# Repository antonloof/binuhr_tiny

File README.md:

# binuhr_tiny
a small binary clock, so cute &lt;3

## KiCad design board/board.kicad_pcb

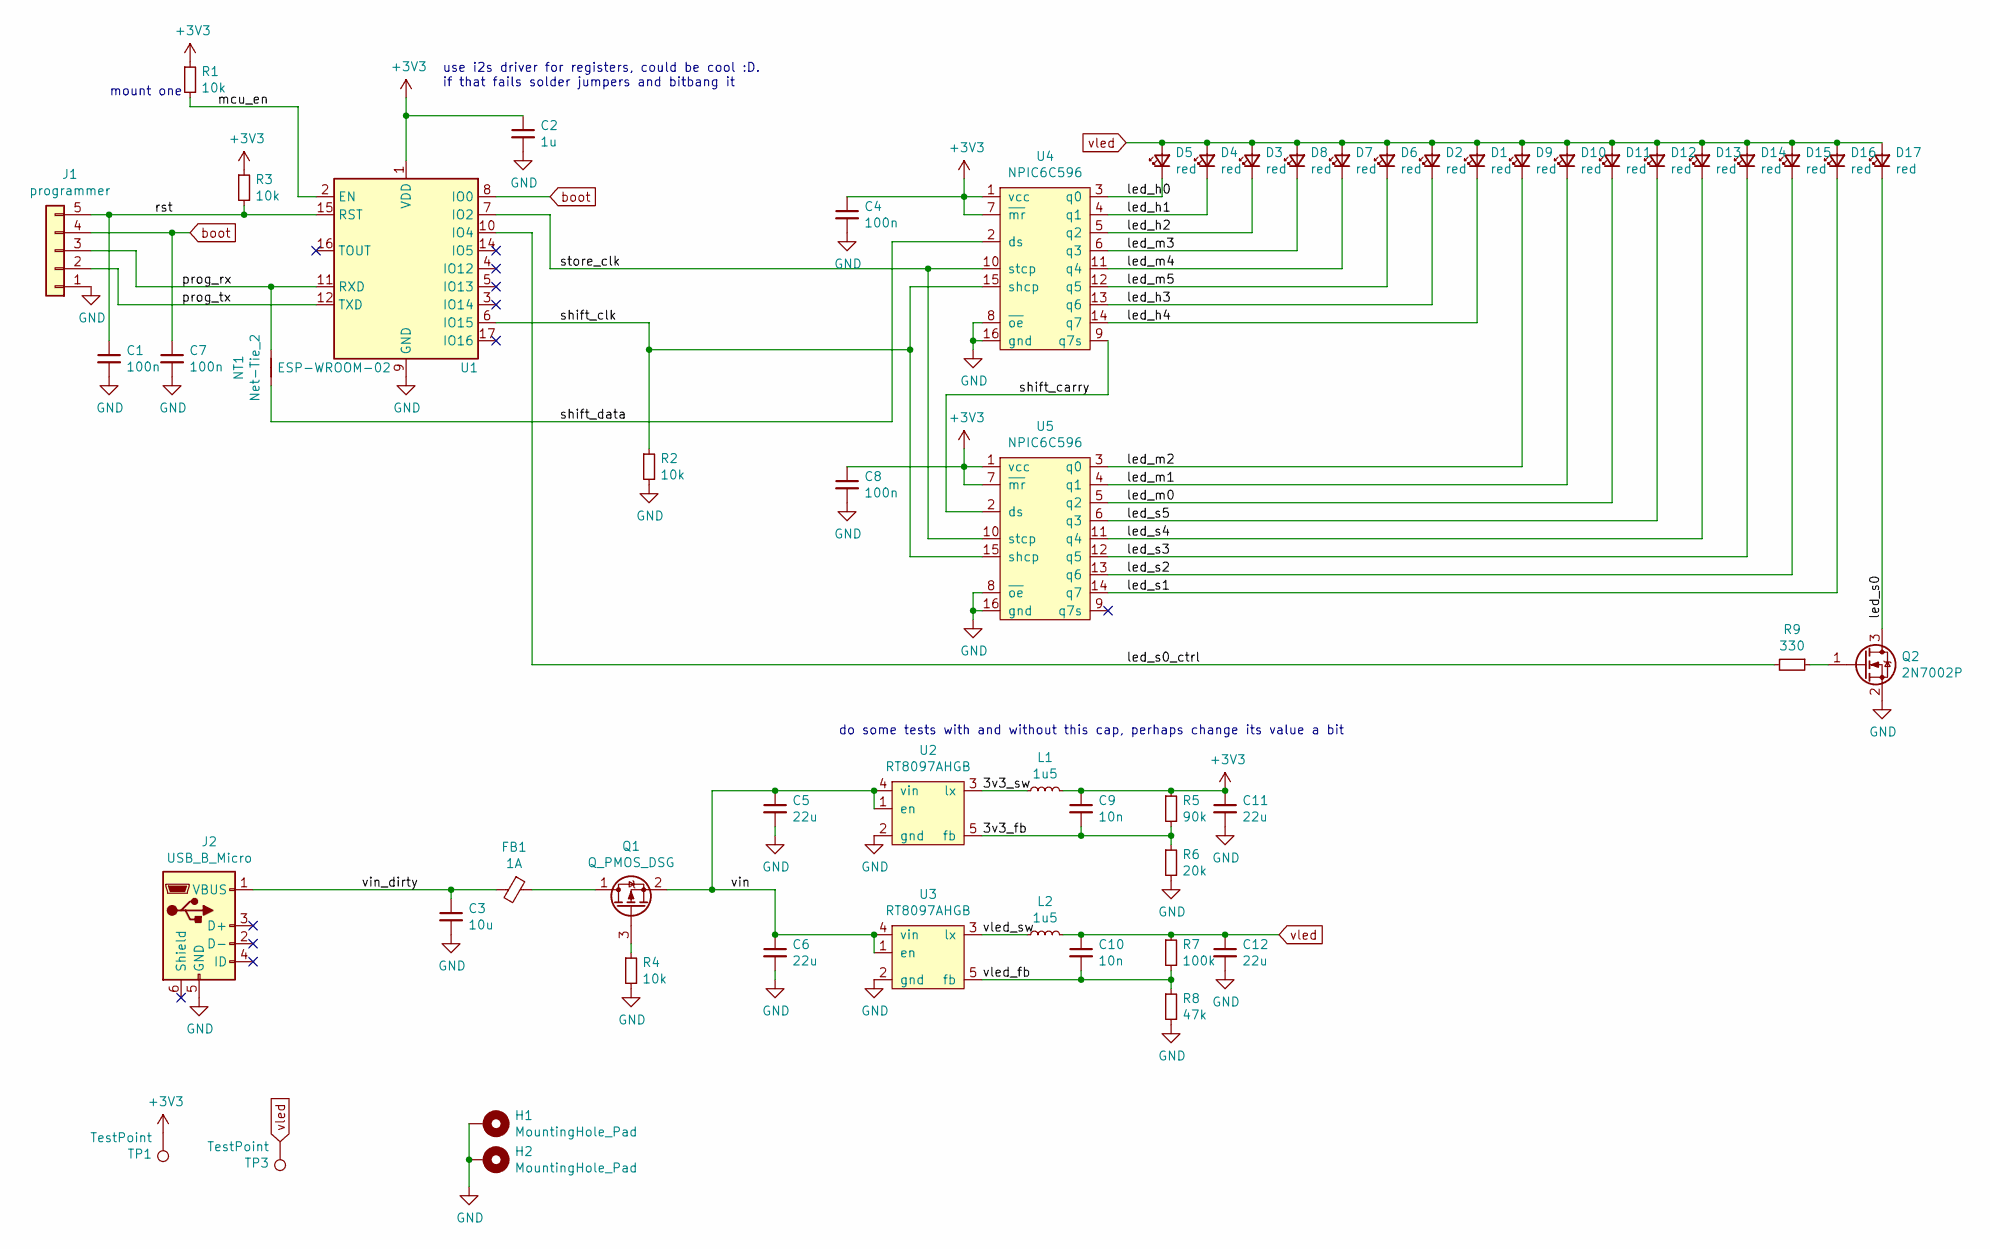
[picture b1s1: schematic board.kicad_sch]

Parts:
C1, C4, C7, C8: 100n; C_0603_1608Metric
C2: 1u; C_0603_1608Metric
C3: 10u; C_0603_1608Metric
C5, C6, C11, C12: 22u; C_0603_1608Metric
C9, C10: 10n; C_0603_1608Metric
D1, D2, D3, D4, D5, D6, D7, D8, D9, D10, D11, D12, D13, D14, D15, D16, D17: red; LED_1210_3225Metric
FB1: 1A; L_0603_1608Metric_Pad1.05x0.95mm_HandSolder
H1, H2: MountingHole_Pad; MountingHole_2.2mm_M2_ISO7380_Pad
J1: programmer; TSM-105-01-L_SH
J2: USB_B_Micro; USB_MICRO_10118193-0001LF
L1, L2: 1u5; L_Sunlord_MWSA0518_5.4x5.2mm
NT1: Net-Tie_2; NetTie-2_SMD_Pad0.5mm
Q1: Q_PMOS_DSG; SOT-23
Q2: 2N7002P; SOT-23
R1, R2, R3, R4: 10k; R_0603_1608Metric
R5: 90k; R_0603_1608Metric
R6: 20k; R_0603_1608Metric
R7: 100k; R_0603_1608Metric
R8: 47k; R_0603_1608Metric
R9: 330; R_0603_1608Metric
TP1, TP3: TestPoint; TestPoint_Pad_D1.5mm
U1: ESP-WROOM-02
U2, U3: RT8097AHGB; SOT-23-5_HandSoldering
U4, U5: NPIC6C596; STC_SOP-16_3.9x9.9mm_P1.27mm

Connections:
+3V3: C2.1, C4.1, C8.1, C9.1, C11.1, L1.2, R1.1, R3.1, R5.1, TP1.1, U1.1 (VDD), U4.1 (vcc), U4.7 (~mr), U5.1 (vcc), U5.7 (~mr)
/3v3_fb: C9.2, R5.2, R6.1, U2.5 (fb)
/3v3_sw: L1.1, U2.3 (lx)
/led_h0: D5.1 (K), U4.3 (q0)
/led_h1: D4.1 (K), U4.4 (q1)
/led_h2: D3.1 (K), U4.5 (q2)
/led_h3: D2.1 (K), U4.13 (q6)
/led_h4: D1.1 (K), U4.14 (q7)
/led_m0: D11.1 (K), U5.5 (q2)
/led_m1: D10.1 (K), U5.4 (q1)
/led_m2: D9.1 (K), U5.3 (q0)
/led_m3: D8.1 (K), U4.6 (q3)
/led_m4: D7.1 (K), U4.11 (q4)
/led_m5: D6.1 (K), U4.12 (q5)
/led_s0: D17.1 (K), Q2.3 (D)
/led_s0_ctrl: R9.2, U1.10 (IO4)
/led_s1: D16.1 (K), U5.14 (q7)
/led_s2: D15.1 (K), U5.13 (q6)
/led_s3: D14.1 (K), U5.12 (q5)
/led_s4: D13.1 (K), U5.11 (q4)
/led_s5: D12.1 (K), U5.6 (q3)
/mcu_en: R1.2, U1.2 (EN)
/prog_rx: J1.3, NT1.2, U1.11 (RXD)
/prog_tx: J1.2, U1.12 (TXD)
/rst: C1.1, J1.5, R3.2, U1.15 (RST)
/shift_carry: U4.9 (q7s), U5.2 (ds)
/shift_clk: R2.1, U1.6 (IO15), U4.15 (shcp), U5.15 (shcp)
/shift_data: NT1.1, U4.2 (ds)
/store_clk: U1.7 (IO2), U4.10 (stcp), U5.10 (stcp)
/vin: C5.1, C6.1, Q1.2 (S), U2.1 (en), U2.4 (vin), U3.1 (en), U3.4 (vin)
/vin_dirty: C3.1, FB1.2, J2.1 (VBUS)
/vled_fb: C10.2, R7.2, R8.1, U3.5 (fb)
/vled_sw: L2.1, U3.3 (lx)
GND: C1.2, C2.2, C3.2, C4.2, C5.2, C6.2, C7.2, C8.2, C11.2, C12.2, H1.1, H2.1, J1.1, J2.5 (GND), Q2.2 (S), R2.2, R4.2, R6.2, R8.2, U1.9 (GND), U1.13 (GND), U1.18 (GND), U1.19 (GND), U2.2 (gnd), U3.2 (gnd), U4.8 (~oe), U4.16 (gnd), U5.8 (~oe), U5.16 (gnd)
unnamed: FB1.1, Q1.1 (D)
unnamed: Q1.3 (G), R4.1
unnamed: Q2.1 (G), R9.1
boot: C7.1, J1.4, U1.8 (IO0)
vled: C10.1, C12.1, D1.2 (A), D2.2 (A), D3.2 (A), D4.2 (A), D5.2 (A), D6.2 (A), D7.2 (A), D8.2 (A), D9.2 (A), D10.2 (A), D11.2 (A), D12.2 (A), D13.2 (A), D14.2 (A), D15.2 (A), D16.2 (A), D17.2 (A), L2.2, R7.1, TP3.1

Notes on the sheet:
mount one
use i2s driver for registers, could be cool :D. if that fails solder jumpers and bitbang it
do some tests with and without this cap, perhaps change its value a bit

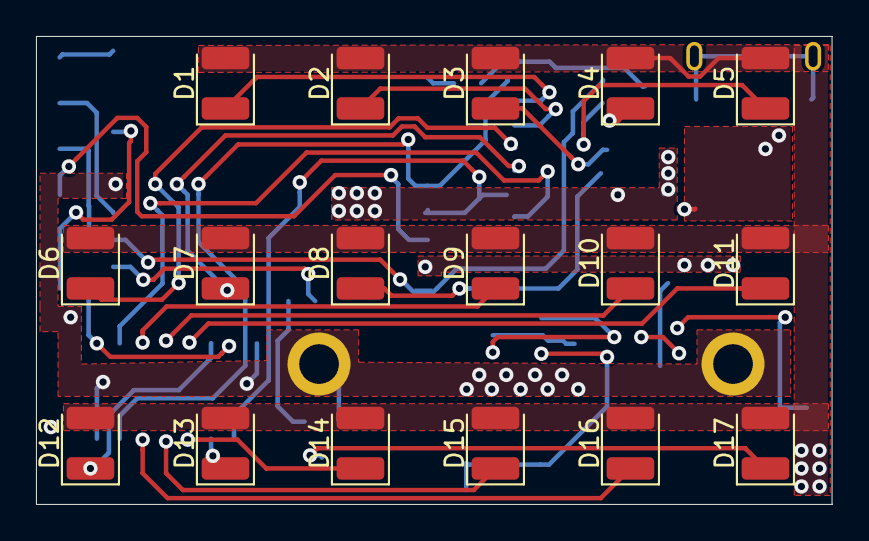
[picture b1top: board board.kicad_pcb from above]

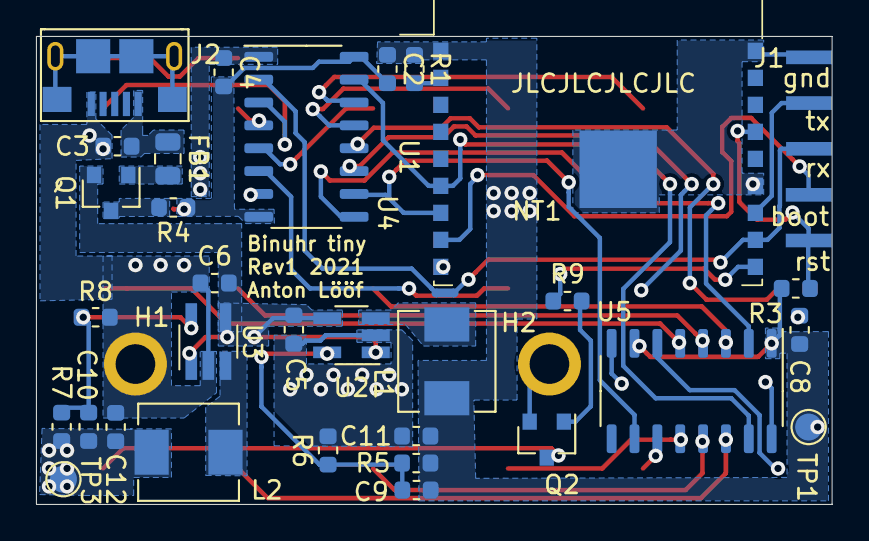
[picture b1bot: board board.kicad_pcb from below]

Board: 2 copper layers, 44.2 x 26.0 mm, 52 parts (35 on the bottom side), 39 nets.

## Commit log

2021-08-21 Add schematic
2021-08-29 Pcb close
2021-08-30 Rev1 PCB
2021-08-30 Add jlc order no silk
2021-10-24 cleanups
2021-10-24 stuffs
2021-11-20 Update transistor partno
2021-11-20 Add v1 sw
    contains basic logic
2021-11-20 Add missing passives from bringup
2021-11-23 Code works
    At least should, can set wifi cred and tz from ui
2022-01-14 Update code to use fancy way to keep track of daylight savings
2022-01-15 Update to kicad6
2022-01-15 remove kicad 5 files
2022-01-15 Make sure to save v6 schematic ...
